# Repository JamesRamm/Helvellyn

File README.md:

Helvellyn
==========

KiCAD schematic and pcb files for the Helvellyn console project.

Helvellyn is a modular, DIY console design by Ramshackle Recording. 
PCB's for various modules will be available from www.ramshacklerecording.com

The backplane PCB for the console is released as an open source project for self-etching/manufacture and improvements, updates etc.

PCB's for the four-module backplane will also be available from Ramshackle Recording.

The Concept
============
The Helvellyn console system is based on the Eurocard and eurorack format and aims to be:

- Modular
- Expandable
- Analogue signal path
- Customisable

Each backplane PCB has space for four 7HP wide eurocard modules, or two 14HP modules.
Modules mate to the backplane via a 32-way DIN connector, which provides the following functionality:

- Two balanced inputs per module (I.e there are allowances for +, - and 0v on each input)
- A direct output (or 2 unbalanced outputs)
- 12 audio buses ('Normal' configuration will be 4 mono auxilliary buses, 3 stereo mix buses and 1 stereo master bus)
- +Ve, -Ve power buses (normally +/-16V)
- Four ground/0V buses (normally used as reference voltage for power, audio, relay/logic power and fader)
- A single, unbalanced output. Normally used to send audio to an external fader.

The backplane can be fixed to a standard 3U Eurorack such as:
http://uk.farnell.com/schroff/24563-131/subrack-3u-175mm-84hp/dp/1370391

With the Helvellyn system, it will be possible to build anything from a single 'lunchbox' rack of individual modules, to a large console with all the usual facilities.

Modules
==========
Ramshackle Recording is actively developing a set of modules which can be used to produce a small-format, high quality mixing desk.
The first modules to be released will be:

- EasyPSU: an 'onboard' PSU for powering a single rack
- Easy69: an easy-to-build high quality EQ, based on the famous Helios type 69.
- ISA-ish: A preamp. Something like the Focusrite ISA, but with modern components.

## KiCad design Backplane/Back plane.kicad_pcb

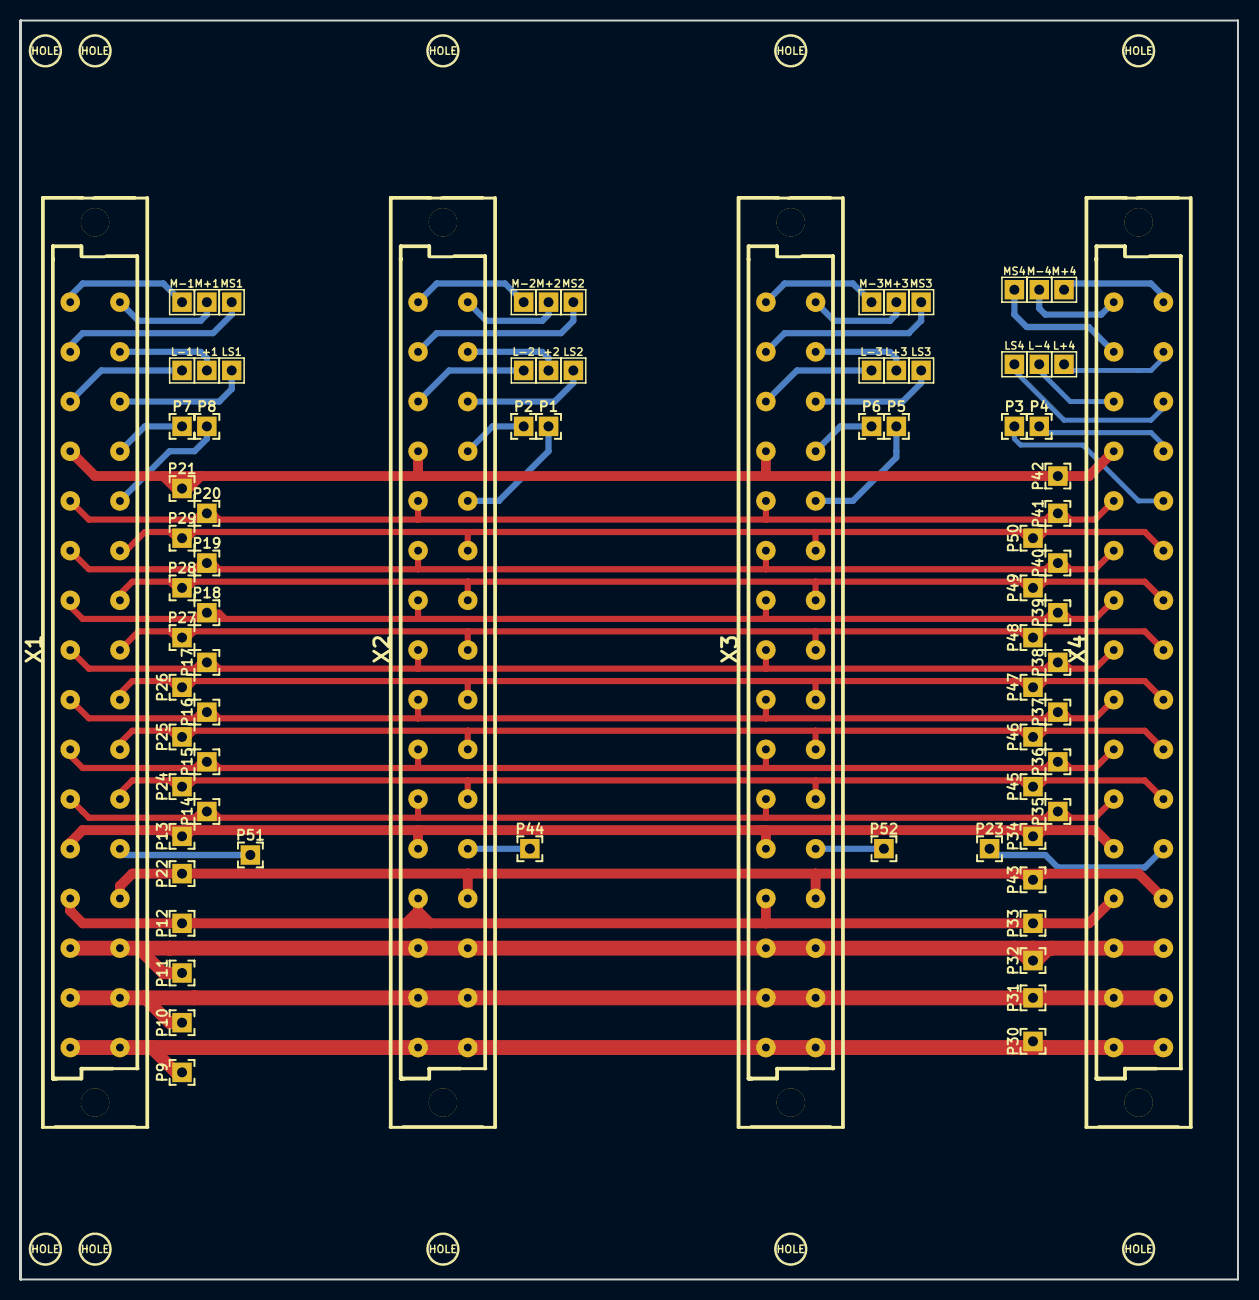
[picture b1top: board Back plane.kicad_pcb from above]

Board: 2 copper layers, 124.5 x 128.7 mm, 90 parts (0 on the bottom side), 56 nets.

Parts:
HOLE: Val**; HOLE_30_nopad
HOLE#2, HOLE#3, HOLE#4, HOLE#5, HOLE#6, HOLE#7, HOLE#8, HOLE#9, HOLE#10: Val**; HOLE_30_nopad
L+1, L+2, L+3, L+4: CONN_1; PIN_ARRAY_1
L-1, L-2, L-3, L-4: CONN_1; PIN_ARRAY_1
LS1, LS2, LS3, LS4: CONN_1; PIN_ARRAY_1
M+1, M+2, M+3, M+4: CONN_1; PIN_ARRAY_1
M-1, M-2, M-3, M-4: CONN_1; PIN_ARRAY_1
MS1, MS2, MS3, MS4: CONN_1; PIN_ARRAY_1
P1, P2, P3, P4, P5, P6, P7, P8, P9, P10, P11, P12, P13, P14, P15, P16, P17, P18, P19, P20, P21, P22, P23, P24, P25, P26, P27, P28, P29, P30, P31, P32, P33, P34, P35, P36, P37, P38, P39, P40, P41, P42, P43, P44, P45, P46, P47, P48, P49, P50, P51, P52: CONN_1; PAD_1
X1, X2, X3, X4: SOCKET-DIN41612-32PIN-2ROW-STYLE1; DIN41612_Female508_32

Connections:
+5V: P22.1, P43.1, X1.13b, X2.13b, X3.13b, X4.13b
+16V: P10.1, P31.1, X1.15a, X1.15b, X2.15a, X2.15b, X3.15a, X3.15b, X4.15a, X4.15b
+48V: P12.1, P33.1, X1.13a, X2.13a, X3.13a, X4.13a
+OUT1: P8.1, X1.5b
+OUT2: P1.1, X2.5b
+OUT3: P5.1, X3.5b
+OUT4: P3.1, X4.5b
-16V: P11.1, P32.1, X1.14a, X1.14b, X2.14a, X2.14b, X3.14a, X3.14b, X4.14a, X4.14b
-OUT1: P7.1, X1.4b
-OUT2: P2.1, X2.4b
-OUT3: P6.1, X3.4b
-OUT4: P4.1, X4.4b
AGND: P9.1, P30.1, X1.16a, X1.16b, X2.16a, X2.16b, X3.16a, X3.16b, X4.16a, X4.16b
AUX1: P19.1, P40.1, X1.6a, X2.6a, X3.6a, X4.6a
AUX2: P28.1, P49.1, X1.7b, X2.7b, X3.7b, X4.7b
AUX3: P20.1, P41.1, X1.5a, X2.5a, X3.5a, X4.5a
AUX4: P29.1, P50.1, X1.6b, X2.6b, X3.6b, X4.6b
B1_L: P15.1, P36.1, X1.10a, X2.10a, X3.10a, X4.10a
B1_R: P24.1, P45.1, X1.11b, X2.11b, X3.11b, X4.11b
B2_L: P16.1, P37.1, X1.9a, X2.9a, X3.9a, X4.9a
B2_R: P25.1, P46.1, X1.10b, X2.10b, X3.10b, X4.10b
B3_L: P17.1, P38.1, X1.8a, X2.8a, X3.8a, X4.8a
B3_R: P26.1, P47.1, X1.9b, X2.9b, X3.9b, X4.9b
B4_L: P18.1, P39.1, X1.7a, X2.7a, X3.7a, X4.7a
B4_R: P27.1, P48.1, X1.8b, X2.8b, X3.8b, X4.8b
FG: P14.1, P35.1, X1.11a, X2.11a, X3.11a, X4.11a
FS1: P44.1, X2.12b
FS2: P23.1, X4.12b
FS3: P51.1, X1.12b
FS4: P52.1, X3.12b
GND: P13.1, P34.1, X1.12a, X2.12a, X3.12a, X4.12a
GNDA: P21.1, P42.1, X1.4a, X2.4a, X3.4a, X4.4a
L+1: L+1.1, X1.2b
L+2: L+2.1, X2.2b
L+3: L+3.1, X3.2b
L+4: L+4.1, X4.2b
L-1: L-1.1, X1.3a
L-2: L-2.1, X2.3a
L-3: L-3.1, X3.3a
L-4: L-4.1, X4.3a
unnamed: M-3.1, X3.1a
unnamed: M+3.1, X3.1b
unnamed: LS3.1, X3.3b
unnamed: MS3.1, X3.2a
unnamed: M+4.1, X4.1b
unnamed: MS4.1, X4.2a
unnamed: M-4.1, X4.1a
unnamed: LS4.1, X4.3b
unnamed: MS2.1, X2.2a
unnamed: M-2.1, X2.1a
unnamed: M+2.1, X2.1b
unnamed: LS2.1, X2.3b
unnamed: MS1.1, X1.2a
unnamed: LS1.1, X1.3b
unnamed: M+1.1, X1.1b
unnamed: M-1.1, X1.1a

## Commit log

2014-08-03 Initial commit
    Initial commit of the backplane files.
    The Helvellyn backplane provides communication between modules, power
    buses etc...
2014-08-03 Create README.md
    First commit
2014-12-17 Easy69 docs
    first commit
2015-08-03 Added schematic
2015-08-03 Better BOM title
